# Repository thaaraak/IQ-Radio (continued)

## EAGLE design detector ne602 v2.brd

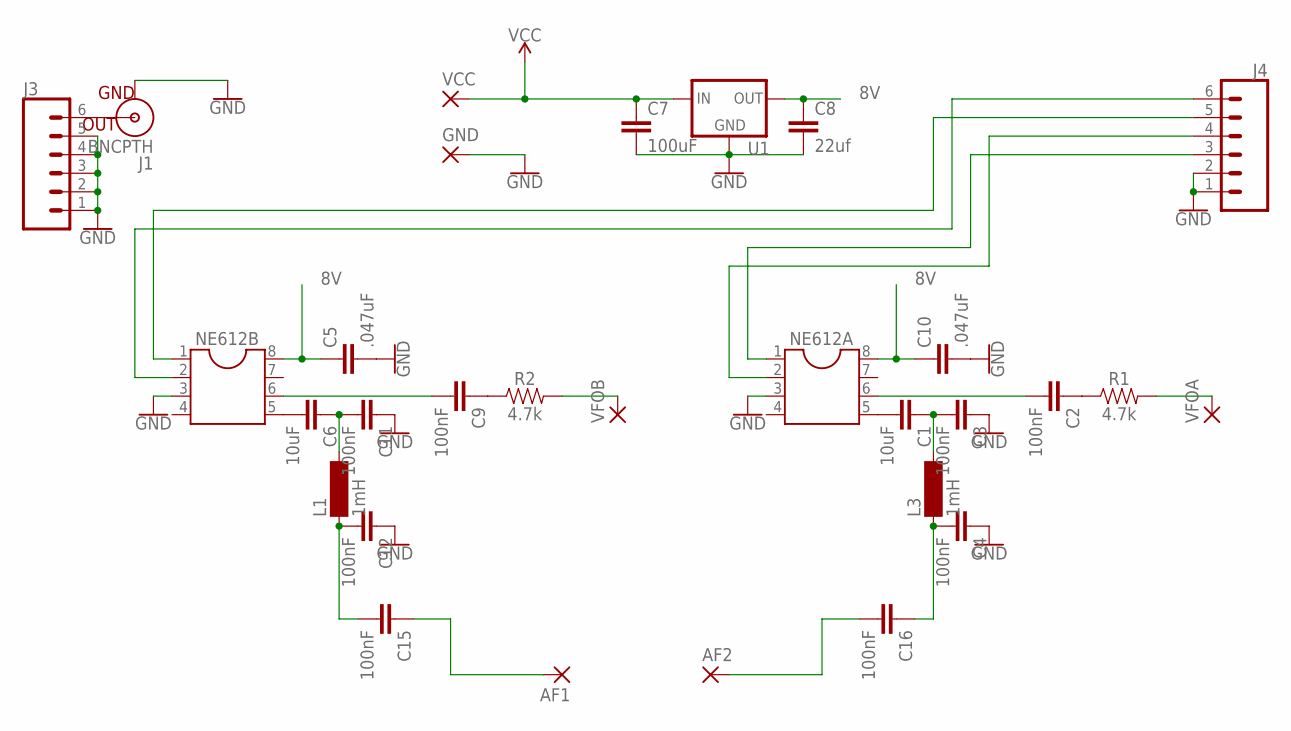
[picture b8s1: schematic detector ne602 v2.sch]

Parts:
AF1, AF2: 3,17/1,1
C1, C6: 10uF; C5B3.5
C2, C3, C4, C9, C11, C12, C15, C16: 100nF; C5B3.5
C5, C10: .047uF; C5B3.5
C7: 100uF; C5B3.5
C8: 22uf; C5B3.5
GND: 3,17/1,1
J1: BNCPTH; BNC
J3, J4: CONN_06SILK_FEMALE_PTH; 1X06
L1, L3: 1mH; BS75
NE612A, NE612B: DIL8; DIL08
R1, R2: 4.7k; AXIAL-0.3
U1: V_REG_78XXTO-92_UNTESTED; TO-92
VCC: 3,17/1,1
VFOA: 3,17/1,1
VFOB: 3,17/1,1

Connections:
8V: C5.1, C8.1, C10.1, NE612A.8, NE612B.8, U1.1 (OUT)
GND: C3.1, C4.1, C5.2, C7.2, C8.2, C10.2, C11.1, C12.1, GND.1, J1.GND, J3.1, J3.2, J3.3, J3.4, J3.5, J4.1, J4.2, NE612A.3, NE612B.3, U1.2 (GND)
unnamed: C1.2, NE612A.5
unnamed: C2.2, NE612A.6
unnamed: C1.1, C3.2, L3.2
unnamed: C4.2, C16.1, L3.1
unnamed: C2.1, R1.P$1 (1)
unnamed: R1.P$2 (2), VFOA.1
unnamed: J4.5, NE612B.1
unnamed: C6.2, NE612B.5
unnamed: C9.2, NE612B.6
unnamed: C6.1, C11.2, L1.2
unnamed: C12.2, C15.2, L1.1
unnamed: C9.1, R2.P$1 (1)
unnamed: R2.P$2 (2), VFOB.1
unnamed: J4.6, NE612B.2
unnamed: J4.3, NE612A.1
unnamed: J4.4, NE612A.2
unnamed: AF1.1, C15.1
unnamed: AF2.1, C16.2
unnamed: J1.S (OUT), J3.6
VCC: C7.1, U1.3 (IN), VCC.1

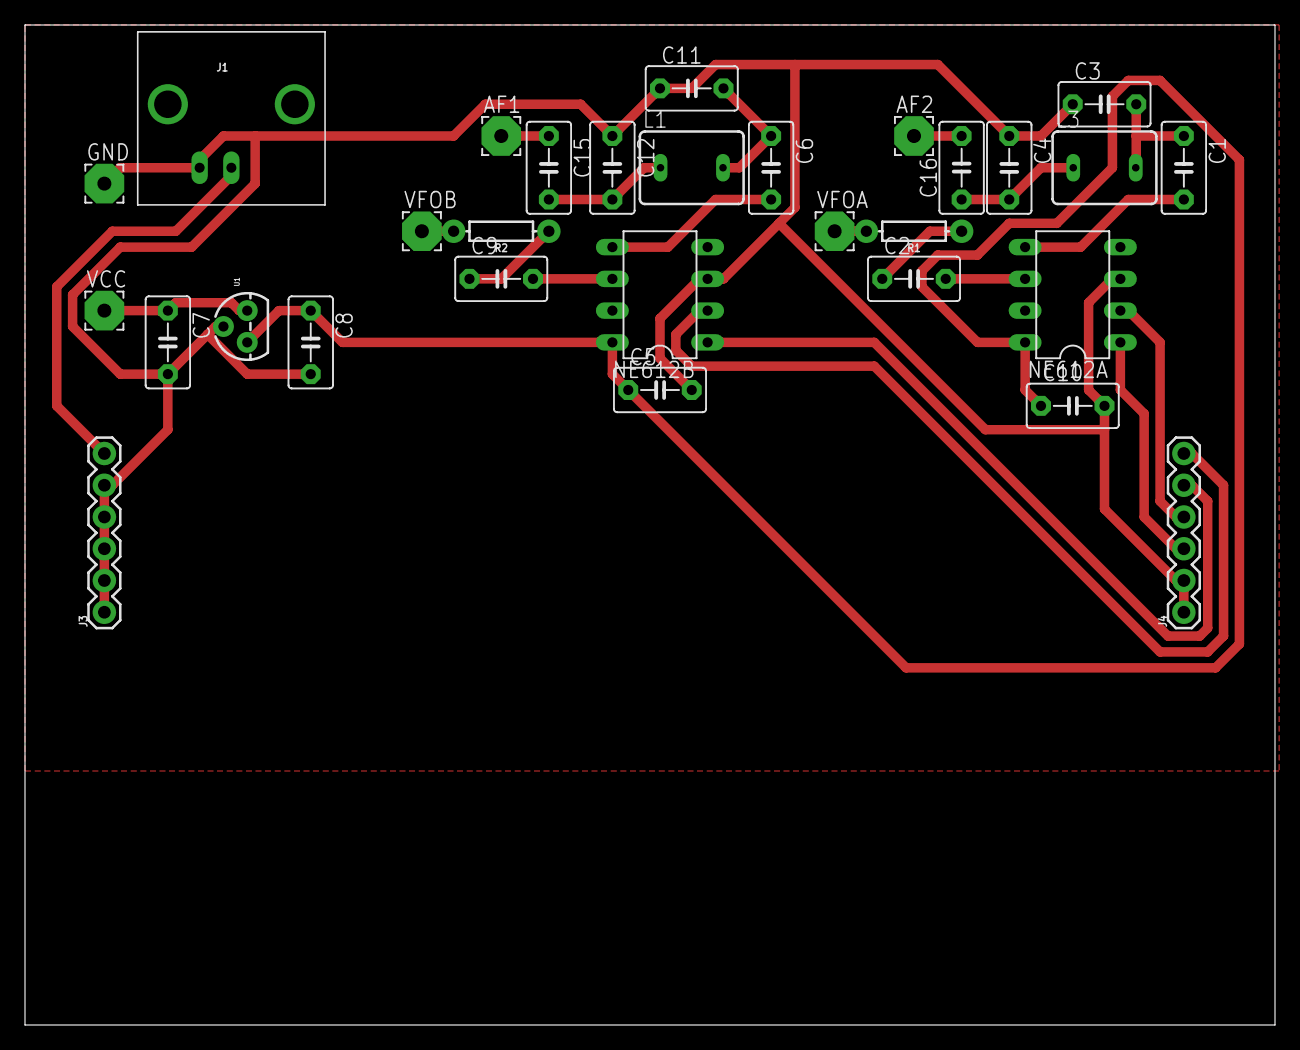
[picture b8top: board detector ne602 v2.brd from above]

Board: 2 copper layers, 100.0 x 80.0 mm, 30 parts (0 on the bottom side), 22 nets.

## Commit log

2020-01-26 New files
2020-01-26 moved files to eagle dir
2020-01-26 si5351 libs
